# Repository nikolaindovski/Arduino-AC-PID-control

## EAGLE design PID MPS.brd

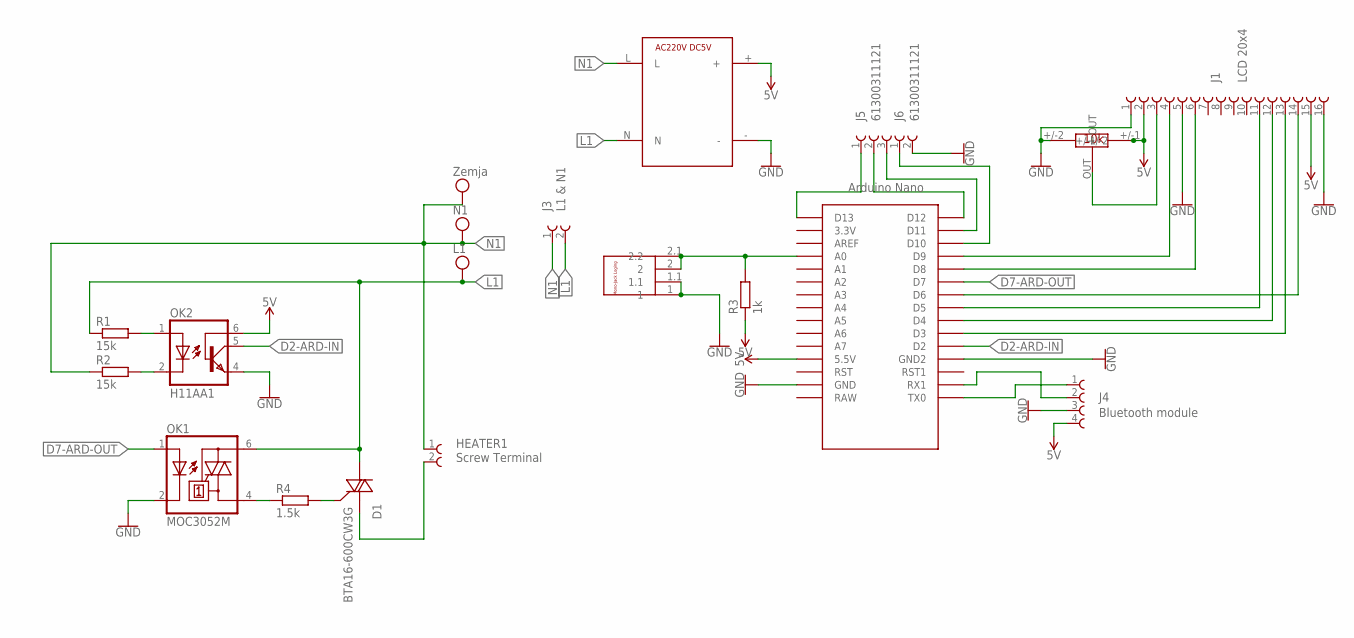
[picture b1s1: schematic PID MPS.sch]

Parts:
D1: BTA16-600CW3G; TO254P1028X482X1968-3
HEATER1: Screw Terminal; 691102710002
J1: LCD 20x4; 61301611121
J3: L1 & N1; 691102710002
J4: Bluetooth module; 61300411121
J5, J6: 61300311121
OK1: MOC3052M; DIL06
OK2: H11AA1; DIL06
R1, R2: 15k; 0207/10
R3: 1k; 0207/10
R4: 1.5k; 0207/10
U$1: NANO
U$2: AC220V-DC5V220V-5VALIEXPESS; 220AC-5DC
U$3: POTENCIOMETAR-GACPOTENCIOMETAR-GAC; POTENCIOMETAR-GAC
U$4: MONO-JACK-LOGING

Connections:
5V: J1.2, J1.15, J4.4, OK2.6 (BAS), R3.1, U$1.5V (5.5V), U$2.+, U$3.+/-1
D2-ARD-IN: OK2.5 (COL), U$1.D2
D7-ARD-OUT: OK1.1 (A), U$1.D7
GND: J1.1, J1.5, J1.16, J4.3, J6.2, OK1.2 (C), OK2.4 (EMI), U$1.GND, U$1.GND1 (GND2), U$2.-, U$3.+/-2, U$4.1, U$4.1.1
L1: D1.2 (MT2), J3.2, OK1.6 (A2), R1.1, U$2.N
N1: HEATER1.1, J3.1, R2.1, U$2.L
unnamed: OK2.1 (A), R1.2
unnamed: OK2.2 (C), R2.2
unnamed: OK1.4 (A1), R4.1
unnamed: D1.3 (G), R4.2
unnamed: J1.4, U$1.D9
unnamed: D1.1 (MT1), HEATER1.2
unnamed: J1.6, U$1.D8
unnamed: J1.11, U$1.D5
unnamed: J1.12, U$1.D4
unnamed: J1.13, U$1.D3
unnamed: J1.14, U$1.D6
unnamed: J1.3, U$3.OUT
unnamed: J4.1, U$1.TX0
unnamed: J4.2, U$1.RX1
unnamed: J5.1, U$1.D13
unnamed: J5.2, U$1.D12
unnamed: J5.3, U$1.D11
unnamed: J6.1, U$1.D10
unnamed: R3.2, U$1.A0, U$4.2, U$4.2.1 (2.2)

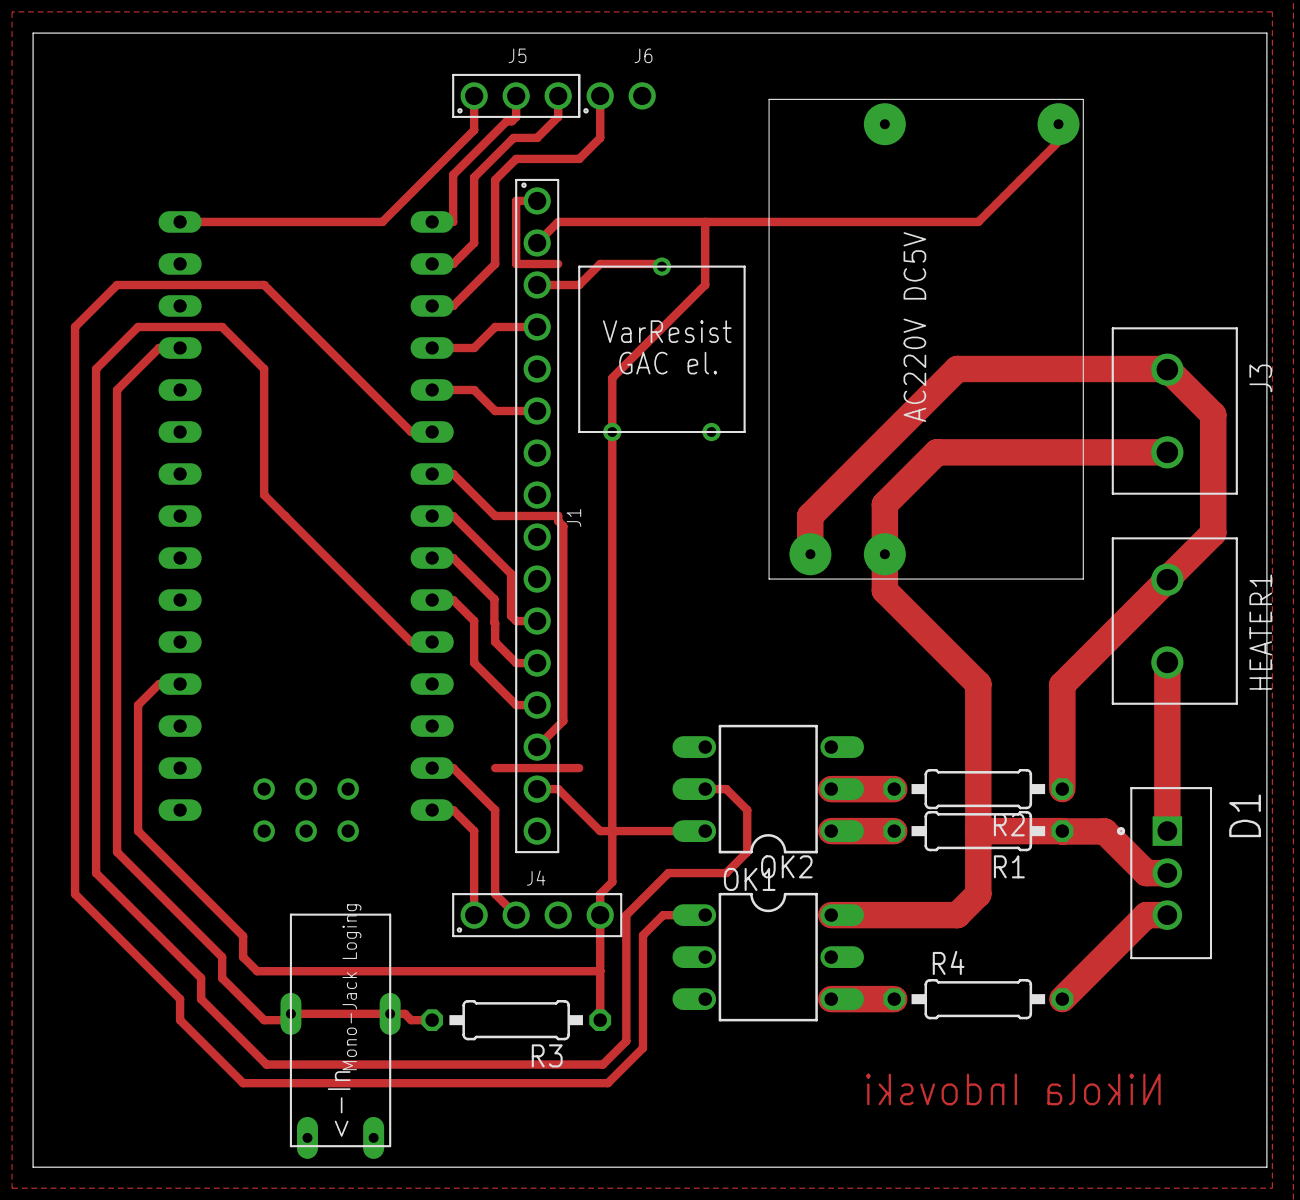
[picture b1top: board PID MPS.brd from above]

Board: 2 copper layers, 74.6 x 68.6 mm, 17 parts (0 on the bottom side), 25 nets.

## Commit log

2022-10-14 Eagle schematics and board design
2022-10-14 Arduino code

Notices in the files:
parts and their libraries:
SparkFun-PowerSymbols: Licensing: Creative Commons ShareAlike 4.0 International - https://creativecommons.org/licenses/by-sa/4.0
